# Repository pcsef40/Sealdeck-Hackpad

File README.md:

My first ever hackpad, made for Stardance Hackclub, the seal deck
It is quite basic but everything here is free of use to anyone in need
contains four MX switches and one OLED screen and an custom pcb board

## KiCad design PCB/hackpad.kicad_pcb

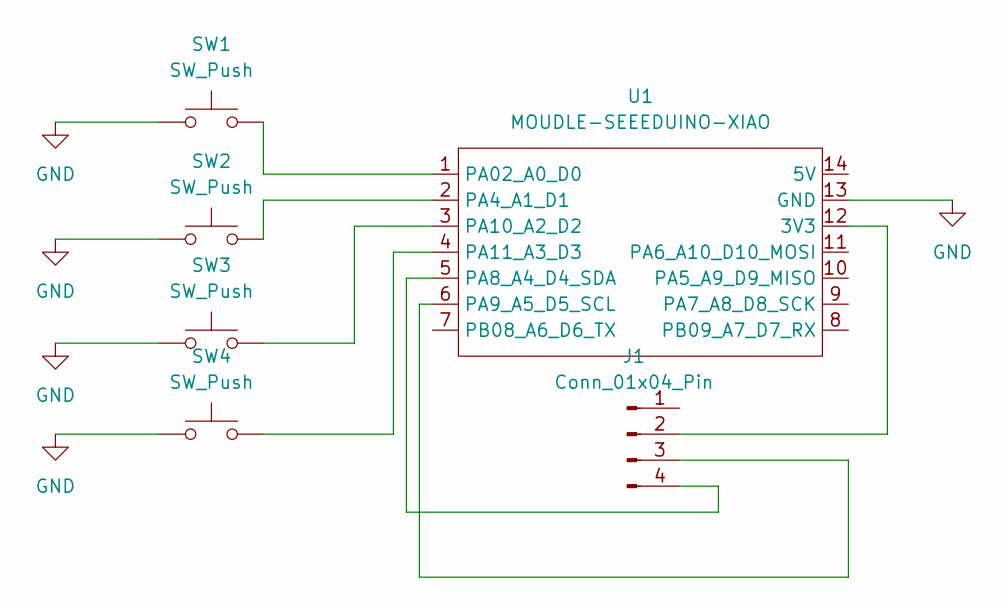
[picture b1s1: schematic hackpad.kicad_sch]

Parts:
J1: Conn_01x04_Pin; FanPinHeader_1x04_P2.54mm_Vertical
SW1, SW2, SW3, SW4: SW_Push; SW_Cherry_MX_1.00u_PCB
U1: MOUDLE-SEEEDUINO-XIAO; XIAO-Generic-Hybrid-14P-2.54-21X17.8MM

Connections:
GND: SW1.1, SW2.1, SW3.1, SW4.1, U1.13 (GND)
unnamed: J1.2, U1.12 (3V3)
unnamed: J1.3, U1.6 (PA9_A5_D5_SCL)
unnamed: J1.4, U1.5 (PA8_A4_D4_SDA)
unnamed: SW1.2, U1.1 (PA02_A0_D0)
unnamed: SW2.2, U1.2 (PA4_A1_D1)
unnamed: SW3.2, U1.3 (PA10_A2_D2)
unnamed: SW4.2, U1.4 (PA11_A3_D3)

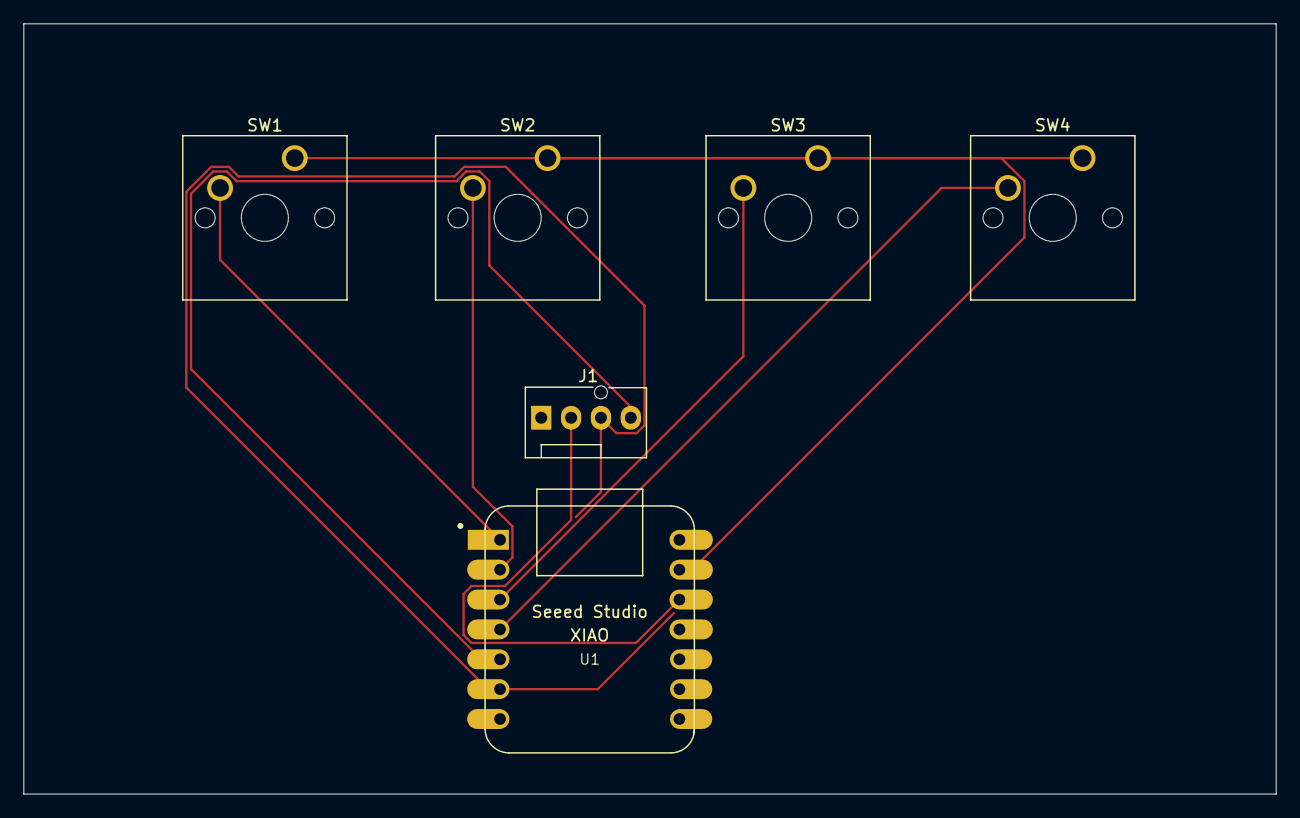
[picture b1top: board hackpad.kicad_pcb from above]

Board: 2 copper layers, 106.5 x 65.5 mm, 6 parts (0 on the bottom side), 8 nets.
